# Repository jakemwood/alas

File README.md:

<picture>
  <source media="(prefers-color-scheme: dark)" srcset="docs/logo-white.svg">
  
</picture>

# ALAS (Automatic Live Audio Streamer)

## Support / Donationware

Commercial support is available for purchase from Ridgeline Radio to support our non-commercial, non-profit radio station.

Stations with budgets over $100,000/year who use ALAS are encouraged to support the project in one of a few ways:

1. Buying the equipment from us
2. Paying monthly subscription fee for the bonded VPN
3. Buying a support package

## About ALAS

ALAS is a hardware/software appliance package that automatically streams and records audio with high reliability.
Whenever audio is present on the sound card input, ALAS will begin streaming and recording. If streaming should stop,
recording will continue, and vice versa. It achieves high straming reliability through the usage of a bonding VPN, with the
designs calling for both a cellular modem and usage of built-in WiFi. ALAS will discontinue streaming and recording after
a configurable period of silence.

## Project Navigation

### alas

The main application, written in Rust, which is deployed onto a Raspberry Pi. It is responsible for:

* Allowing for easy field configuration of the appliance via a WiFi access point
* Managing the WiFi state once configured by the end user
* Manging the cellular state once configured by the end user
* Continuously monitoring input audio signal to determine when audio is being input
* Stream audio to Icecast when audio is present
* Providing a web interface for end users to administer the device
* Ensuring audio traffic is using the appropriate Engarde Wireguard interface

### cad

You'll find FreeCAD and STEP files in this folder for fabricating the rack mountable case.

### docs

You'll find instructions on how to assemble the hardware and user's guide in this folder. Documentation for software
is generally found adjacent to these components.

### frontend

To save bandwidth, a static frontend is available with a configurable backend. The static frontend is found here.
This is distinct from the "deployed frontend," which is used during the initial configuration of the network settings
on the Raspberry Pi.

### infrastructure

This is the Terraform used to create the bonding VPN servers in Microsoft Azure. 

## ALAS Software Components

### alas_lib

alas_lib is meant to serve as the "brains" of the operation. However, there is some serious
separation of concerns issues here, as the main state of the application is actually held in `alas`.

### alas

This is the monolithic application that runs on the Raspberry Pi.

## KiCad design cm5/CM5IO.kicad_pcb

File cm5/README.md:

# Alas IO Board

A custom Raspberry Pi 5 Compute Module board for Alas

Forked from the open source Raspberry Pi 5 Compute Module IO board

Modified by [Jurgen Bayer](https://www.fiverr.com/jurgenexpert/design-pcb-for-raspberry-pi-compute-module-cm4-cm5-carrier-board-cm5-io-board)

# File structure

`AlasIO` - the KiCAD files that are relevant.
`Logo Footprints` - the KiCAD footprints for the Ridgeline Radio and ALAS logos

All others are earlier attempts, revisions, drafts, etc.

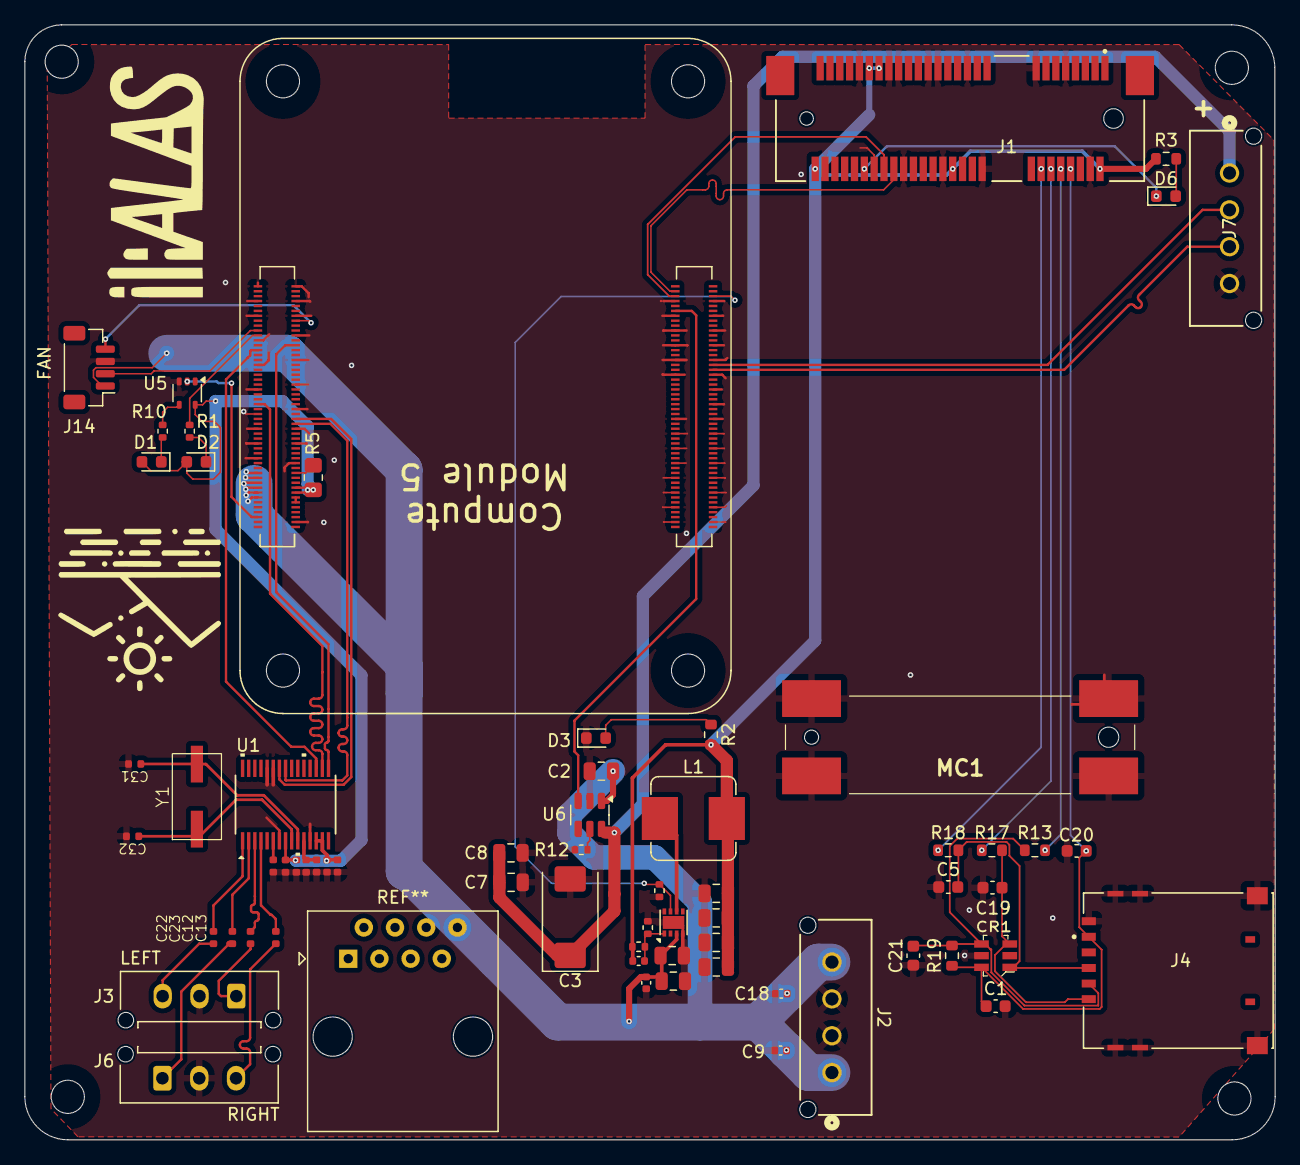
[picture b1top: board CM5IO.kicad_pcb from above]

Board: 4 copper layers, 101.9 x 90.8 mm, 69 parts (0 on the bottom side), 50 nets.

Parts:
C1: 0.1uF; C_0603_1608Metric
C2, C4, C6, C7, C8, C14, C15, C16, C17: 10u; C_0805_2012Metric
C3: 100uF; CP_EIA-7343-31_Kemet-D
C5, C19, C20, C21: 33pF; C_0603_1608Metric
C9, C10, C18: 100n; C_0402_1005Metric
C11: 4.7nF; C_0402_1005Metric
C12, C13, C22, C23, C25, C27, C29: 10uF; C_0402
C24: 1uF; C_0402
C26, C28, C30: 100nF; C_0402
C31, C32: 15pF; C_0402
CR1: DALC208SC6; SOT23-6L
D1, D3, D6: LED Red; LED_0603_1608Metric
D2: LED Green; LED_0603_1608Metric
H2, H3, H6, H8: MountingHole; MountingHole_2.7mm_M2.5_DIN965
J1: 67910-5700; MOLEX_67910-5700
J2: 1x4; CONN_SD-43650-006_04_MOL 1x4
J3, J6: Conn_01x03; Molex_Micro-Fit_3.0_43650-0315_1x03_P3.00mm_Vertical
J4: 0786463001; MOLEX_0786463001
J7: Conn_01x04; CONN_SD-43650-006_04_MOL 1x4
J14: JST_SHBM04B-SRSS-TB; JST_SH_BM04B-SRSS-TB_1x04-1MP_P1.00mm_Vertical
L1: 2.2uH; L_Bourns_SRP7028A_7.3x6.6mm
MC1: 480994000
Module1: ComputeModule5-CM5; Raspberry-Pi-5-Compute-Module
R1, R10: 1k; R_0402_1005Metric
R2, R3: 330; R_0603_1608Metric
R5: 0R; R_0805_2012Metric_Pad1.20x1.40mm_HandSolder
R12: 15K 1%; R_0402_1005Metric
R13, R17, R18: 22R; R_0603_1608Metric
R14: 100K 1%; R_0402_1005Metric
R15: 10K 1%; R_0402_1005Metric
R16: 2.2K 1%; R_0402_1005Metric
R19: 15K; R_0603_1608Metric
U1: PCM1863DBT; DBT30_TEX
U5: 74LVC1G07SE-7; SOT-353_SC-70-5
U6: AP22653W6; SOT-23-6
U8: AP3441SHE-7B; DFN-8-1EP_2x2mm_P0.5mm_EP1.05x1.75mm
Y1: Crystal (24.576MHz); S47SMD

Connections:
/+3.3v: C25.2, C26.2, C27.2, C28.1, D1.2 (A), D2.2 (A), Module1.84 (+3.3v_(Output)), Module1.86 (+3.3v_(Output)), R5.1, U1.8 (AVDD), U1.13 (DVDD), U1.14 (IOVDD), U5.5 (VCC)
/+5v: C2.1, C4.1, C6.1, C9.1, C10.1, C18.1, J2.1, J2.4, J14.1, Module1.77 (+5v_(Input)), Module1.79 (+5v_(Input)), Module1.81 (+5v_(Input)), Module1.83 (+5v_(Input)), Module1.85 (+5v_(Input)), Module1.87 (+5v_(Input)), U6.1 (IN), U8.3 (VIN)
/CM5_GPIO ( Ethernet, GPIO, SDCARD)/+1.8v: Module1.88 (+1.8v_(Output)), Module1.90 (+1.8v_(Output))
/CM5_GPIO ( Ethernet, GPIO, SDCARD)/Audio/LDO: C29.2, C30.1, U1.11 (LDO)
/CM5_GPIO ( Ethernet, GPIO, SDCARD)/Audio/LN: C22.1, J3.3
/CM5_GPIO ( Ethernet, GPIO, SDCARD)/Audio/LP: C12.1, J3.1
/CM5_GPIO ( Ethernet, GPIO, SDCARD)/Audio/RN: C23.1, J6.1
/CM5_GPIO ( Ethernet, GPIO, SDCARD)/Audio/RP: C13.1, J6.3
/CM5_GPIO ( Ethernet, GPIO, SDCARD)/Audio/VIN1M: C22.2, U1.1 (VINL2/VIN1M)
/CM5_GPIO ( Ethernet, GPIO, SDCARD)/Audio/VIN1P: C12.2, U1.3 (VINL1/VIN1P)
/CM5_GPIO ( Ethernet, GPIO, SDCARD)/Audio/VIN2M: C23.2, U1.2 (VINR2/VIN2M)
/CM5_GPIO ( Ethernet, GPIO, SDCARD)/Audio/VIN2P: C13.2, U1.4 (VINR1/VIN2P)
/CM5_GPIO ( Ethernet, GPIO, SDCARD)/Audio/XI: C31.1, U1.10 (XI), Y1.2
/CM5_GPIO ( Ethernet, GPIO, SDCARD)/Audio/XO: C32.1, U1.9 (XO), Y1.1
/CM5_GPIO ( Ethernet, GPIO, SDCARD)/GPIO2: Module1.58 (GPIO2), U1.23 (MOSI/SDA)
/CM5_GPIO ( Ethernet, GPIO, SDCARD)/GPIO3: Module1.56 (GPIO3), U1.24 (MC/SCL)
/CM5_GPIO ( Ethernet, GPIO, SDCARD)/GPIO18: Module1.49 (GPIO18), U1.17 (BCK)
/CM5_GPIO ( Ethernet, GPIO, SDCARD)/GPIO19: Module1.26 (GPIO19), U1.16 (LRCK)
/CM5_GPIO ( Ethernet, GPIO, SDCARD)/GPIO20: Module1.27 (GPIO20), U1.18 (DOUT)
/CM5_GPIO ( Ethernet, GPIO, SDCARD)/GPIO_VREF: Module1.78 (GPIO_VREF(1.8v/3.3v_Input)), R5.2
/CM5_GPIO ( Ethernet, GPIO, SDCARD)/PWM: J14.2, Module1.19 (FAN_PWM)
/CM5_GPIO ( Ethernet, GPIO, SDCARD)/TACHO: J14.4, Module1.16 (FAN_TACHO)
/CM5_GPIO ( Ethernet, GPIO, SDCARD)/nPWR_LED: Module1.95 (LED_nPWR), U5.2
/CM5_HighSpeed/PCIE_PWR_EN: Module1.106 (PCIE_PWR_EN), R14.1, U8.7 (EN)
/CM5_HighSpeed/USB2_N: J1.36, Module1.103 (USB2_N)
/CM5_HighSpeed/USB2_P: J1.38, Module1.105 (USB2_P)
/CM5_HighSpeed/USB3-0-D_N: J7.3, Module1.136 (USB3-0-D_N)
/CM5_HighSpeed/USB3-0-D_P: J7.2, Module1.134 (USB3-0-D_P)
/CM5_HighSpeed/VBUS: C3.1, C7.1, C8.1, J7.1, U6.6 (OUT)
/CM5_HighSpeed/VBUS_EN: Module1.111 (VBUS_EN), U6.3 (EN)
/Cellular/FB: C11.2, R15.2, R16.1, U8.1 (FB)
/Cellular/LED_WWAN: D6.1 (K), J1.42
/Cellular/M2_3v3: C11.1, C14.1, C15.1, C16.1, C17.1, J1.2, J1.24, J1.39, J1.41, J1.52, L1.2, R2.2, R3.2, R15.1
/Cellular/SIM_CLK: J1.12, R17.1
/Cellular/SIM_DATA: J1.10, R13.2
/Cellular/SIM_RST: J1.14, R18.1
/Cellular/SIM_VDD: C1.1, C20.1, CR1.6 (I/O4), J1.8, J4.C1 (VCC), R19.1
GND: C1.2, C2.2, C3.2, C4.2, C5.1, C6.2, C7.2, C8.2, C9.2, C10.2, C14.2, C15.2, C16.2, C17.2, C18.2, C19.1, C20.2, C21.2, C24.1, C25.1, C26.1, C27.1, C28.2, C29.1, C30.2, C31.2, C32.2, CR1.5 (REF1), D3.1 (K), J1.4, J1.9, J1.15, J1.18, J1.21, J1.26, J1.27, J1.29, J1.34, J1.35, J1.37, J1.40, J1.43, J1.50, J2.2, J2.3, J3.2, J4.C5 (GND), J4.G1 (GND__1), J4.G2 (GND__2), J4.G3 (GND__3), J4.G4 (GND__4), J4.G5 (GND__5), J4.G6 (GND__6), J6.2, J7.4, J14.3, MC1.1, MC1.2, MC1.3, MC1.4, Module1.1 (GND), Module1.2 (GND), Module1.7 (GND), Module1.8 (GND), Module1.13 (GND), Module1.14 (GND), Module1.22 (GND), Module1.23 (GND), Module1.32 (GND), Module1.33 (GND), Module1.42 (GND), Module1.43 (GND), Module1.52 (GND), Module1.53 (GND), Module1.59 (GND), Module1.60 (GND), Module1.65 (GND), Module1.66 (GND), Module1.71 (GND), Module1.74 (GND), Module1.98 (GND), Module1.107 (GND), Module1.108 (GND), Module1.113 (GND), Module1.114 (GND), Module1.119 (GND), Module1.120 (GND), Module1.125 (GND), Module1.126 (GND), Module1.131 (GND), Module1.132 (GND), Module1.137 (GND), Module1.138 (GND), Module1.144 (GND), Module1.150 (GND), Module1.155 (GND), Module1.156 (GND), Module1.161 (GND), Module1.162 (GND), Module1.167 (GND), Module1.168 (GND), Module1.173 (GND), Module1.174 (GND), Module1.179 (GND), Module1.180 (GND), Module1.185 (GND), Module1.186 (GND), Module1.191 (GND), Module1.192 (GND), Module1.197 (GND), Module1.198 (GND), R12.2, R14.2, R16.2, U1.7 (AGND), U1.12 (DGND), U1.25 (MS/AD), U1.26 (MD0), U5.3 (GND), U6.2 (GND), U8.4 (PGND), U8.8 (SGND), U8.9 (PAD)
unnamed: C5.2, CR1.1 (I/O1), J4.C2 (RST), R18.2
unnamed: C19.2, CR1.3 (I/O2), J4.C3 (CLK), R17.2
unnamed: C21.1, CR1.4 (I/O3), J4.C7 (I/O), R13.1, R19.2
unnamed: D1.1 (K), R10.1
unnamed: D2.1 (K), R1.1
unnamed: D3.2 (A), R2.1
unnamed: D6.2 (A), R3.1
unnamed: Module1.21 (LED_nACT), R1.2
unnamed: R10.2, U5.4
unnamed: C24.2, U1.6 (VREF)
unnamed: R12.1, U6.5 (ILIM)
unnamed: L1.1, U8.6 (LX)

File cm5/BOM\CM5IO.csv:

"Reference","Value","Footprint","Datasheet","Qty","Field4","Field5","Field6","Field7","Field8","Part Description","DNP"
"C1","0.1uF","Capacitor_SMD:C_0603_1608Metric","~","1","","","","","","",""
"C2,C4,C6,C7,C8,C14,C15,C16,C17","10u","Capacitor_SMD:C_0805_2012Metric","https://search.murata.co.jp/Ceramy/image/img/A01X/G101/ENG/G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","9","Digikey","490-14381-1-ND","GRM21BR71A106KA73L","Murata","111893011","10uF 10% 10V Ceramic Capacitor X7R 0805 (2012 Metric)",""
"C3","100uF","Capacitor_Tantalum_SMD:CP_EIA-7343-31_Kemet-D","~","1","Mouser","667-EEF-CX0J101R","","Panasonic","","Capacitor, SP-Cap, 100u, 6.3V, 15mR ESR",""
"C5,C19,C20,C21","33pF","Capacitor_SMD:C_0603_1608Metric","~","4","","","","","","",""
"C9,C10,C18,C23,C25,C26,C29,C31","100n","Capacitor_SMD:C_0402_1005Metric","https://search.murata.co.jp/Ceramy/image/img/A01X/G101/ENG/G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","8","Farnell","2611911","RM EMK105 B7104KV-F","TAIYO YUDEN EUROPE GMBH","110091611","0.1uF 10% 16V Ceramic Capacitor X7R 0402 (1005 Metric)",""
"C11","4.7nF","Capacitor_SMD:C_0402_1005Metric","~","1","","","","","","4.7nF capacitor 0402",""
"C12,C13","1uF","digikey-footprints:0603","~","2","","","","","","",""
"C24","1uF","digikey-footprints:0805","~","1","","","","","","",""
"C27,C28,C30","10uF","Capacitor_SMD:CP_Elec_6.3x5.9","~","3","","","","","","",""
"CR1","DALC208SC6","digikey-footprints:SOT23-6L","DALC208SC6","1","","","","","","",""
"D1,D3,D4,D6","LED Red","LED_SMD:LED_0603_1608Metric","http://optoelectronics.liteon.com/upload/download/DS22-2000-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","4","Digikey ","LTST-S270KRKT","SML-A12U8TT86Q","Rohm","650295101","Red 620nm LED Indication - Discrete 2.2V 2-SMD, No Lead",""
"D2","LED Green","LED_SMD:LED_0603_1608Metric","http://optoelectronics.liteon.com/upload/download/DS22-2000-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","1","Digikey ","LTST-S270KGKT","SML-A12M8TT86N","Rohm","650263301","Green 572nm LED Indication - Discrete 2.2V 2-SMD, No Lead",""
"J1","67910-5700","0679105700:MOLEX_67910-5700","","1","","","","","","",""
"J2","B2B-XH-A_LF__SN_","digikey-footprints:PinHeader_1x2_P2.5mm_Drill1.1mm","http://www.jst-mfg.com/product/pdf/eng/eXH.pdf","1","","","","","","",""
"J4","0786463001","0786463001:MOLEX_0786463001","","1","","","","","","",""
"J5","USB3_A","Connector_USB:C168717","~","1","","","","","","",""
"J6","Conn_02x03_Counter_Clockwise","Connector_PinHeader_2.54mm:PinHeader_2x03_P2.54mm_Vertical","~","1","","","","","","",""
"J7","Conn_01x04","Connector_JST:JST_EH_B4B-EH-A_1x04_P2.50mm_Vertical","~","1","","","","","","",""
"J14","JST_SHBM04B-SRSS-TB","Connector_JST:JST_SH_BM04B-SRSS-TB_1x04-1MP_P1.00mm_Vertical","","1","","SHBM04B-SRSS-TB","SHBM04B-SRSS-TB","JST","","4 pin vertical 1mm pitch connector",""
"L1","2.2uH","CM5IO:L_Bourns_SRP5030CC","https://www.bourns.com/docs/product-datasheets/srp5030cc.pdf","1","","SRP5030CC-2R2M","SRP5030CC-2R2M","Bourns","","Inductor, SMT, 2520, 2u2, IRMS=7A, ISAT=8A, DCR=0.032R",""
"M1","M.2 Screw","","","1","","","","","","M.2 Screw",""
"M2,M3,M4,M5","M.2 Solder Nut","","","4","","","","","","Solder nut for M.2 slot",""
"MC1","~","KiCad:480994000","","1","","","","","","",""
"Module1","ComputeModule5-CM5","CM5IO:Raspberry-Pi-5-Compute-Module","","1","Amphenol","2x 10164227-1001A1RLF","2x 10164227-1001A1RLF","Hirose","","100 Position Connector Receptacle, Center Strip Contacts Surface Mount Gold",""
"R1,R10","1k","Resistor_SMD:R_0402_1005Metric","https://fscdn.rohm.com/en/products/databook/datasheet/passiv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","2","Farnell","9239235","RK73H1ETTP1001F","KOA EUROPE GMBH","125049511","Resistor 1K M1005 1% 63mW",""
"R2,R3,R11","330","Resistor_SMD:R_0603_1608Metric","~","3","","","","","","",""
"R5","0R","Resistor_SMD:R_0805_2012Metric_Pad1.20x1.40mm_HandSolder","https://fscdn.rohm.com/en/products/databook/datasheet/passiv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","1","Farnell","9233750","MCR10EZPJ000","Rohm","121629591","Resistor 0R M2012 5% ",""
"R12","15K 1%","Resistor_SMD:R_0402_1005Metric","https://fscdn.rohm.com/en/products/databook/datasheet/passiv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","1","Farnell","9239375","MCR01MZPF1502","Rohm","120891581","Resistor 15K M1005 1% 63mW",""
"R13,R17,R18","22R","Resistor_SMD:R_0603_1608Metric","~","3","","","","","","",""
"R14","100K 1%","Resistor_SMD:R_0402_1005Metric","https://fscdn.rohm.com/en/products/databook/datasheet/passiv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","1","Farnell","","MCR01MZPF1003","Rohm","","Resistor 100K M1005 1% 63mW",""
"R15","10K 1%","Resistor_SMD:R_0402_1005Metric","https://fscdn.rohm.com/en/products/databook/datasheet/passiv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","1","Farnell","","MCR01MZPF1002","Rohm","","Resistor 10K M1005 1% 63mW",""
"R16","2.2K 1%","Resistor_SMD:R_0402_1005Metric","https://fscdn.rohm.com/en/products/databook/datasheet/passiv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","1","Farnell","","","","","Resistor 2.2K M1005 1% 63mW",""
"R19","15K","Resistor_SMD:R_0603_1608Metric","~","1","","","","","","",""
"U1","CAT24C128","Package_SO:SOIC-8_5.3x6.2mm_P1.27mm","https://www.onsemi.com/pub/Collateral/CAT24C128-D.PDF","1","","","","","","",""
"U2","TLV320ADC6120IRTER","TLV320ADC6120IRTER:IC_TLV320ADC6120IRTER","","1","","","","","","",""
"U5","74LVC1G07SE-7","Package_TO_SOT_SMD:SOT-353_SC-70-5","https://www.diodes.com/assets/Datasheets/74LVC1G07.pdf","1","Farnell","2425492","74LVC1G07SE-7","Diodes","","Buffer, Non-Inverting 1 Element 1 Bit per Element Open Drain Output SOT-353",""
"U6","AP22653W6","Package_TO_SOT_SMD:SOT-23-6","https://www.diodes.com/assets/Datasheets/AP255x.pdf","1","Digikey","31-AP22653W6-7CT-ND","AP22653W6","Diodes","","Power Switch/Driver 1:1 P-Channel 2.1A SOT-23-6",""
"U8","AP3441SHE-7B","Package_DFN_QFN:DFN-8-1EP_2x2mm_P0.5mm_EP1.05x1.75mm","https://www.diodes.com/assets/Datasheets/AP3441-L.pdf","1","","AP3441SHE-7B","AP3441SHE-7B","Diodes","","3A DC-DC converter",""

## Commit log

2024-12-19 Checkpoint -- it compiles and writes stuff to the LCD display
2024-12-19 Initial AI frontend
2024-12-19 Formatting
2024-12-19 Success at connecting to access point via web browser
2024-12-19 Remove dead imports
2024-12-19 Working volume meter
2024-12-19 Relatively working LCD screen!
2024-12-19 too many changes
2024-12-19 Much nicer frontend
2024-12-19 Refactor to fix unit tests and clean up screen import cycles
2024-12-19 small justfile add for frontend
2024-12-19 install alsa
2024-12-19 install alsa 2
2024-12-19 install lib-alsa
2024-12-19 libudev install
2024-12-21 Well it WAS working
2024-12-22 approximately the correct configuration for working audio
2024-12-22 Write software shutdown to display on graceful program exit
2024-12-22 Audio is in a great spot now with Icecast and recording working via the bus
2024-12-23 Remove .idea from git
2024-12-23 Rename web to alas, and ridgeline references to alas
2024-12-23 Setup script + other things
2024-12-23 IP address screen works, but state mgmt needs a ton of work
2024-12-23 Add just test
2024-12-23 Formatting + renames
2024-12-23 Add ability to create the configuration hotspot
2024-12-23 Unit tests for menu screen and whatnot
2024-12-30 * Refactors on WiFi configuration situation * Fixes on the configuration menu
2024-12-30 Enormous re-org
2024-12-30 re-org part 2
2024-12-30 Working SSE for sending volume data but it is *really* fast, needs base64 encoding for floats
2024-12-30 some rust fixes
2024-12-31 Add cad files
2025-01-31 add throttle for voulme messages
2025-02-02 Enlarge pockets for buttons and LEDs on display, fix C14 size, fix height of base, improve the top
2025-03-03 something terrible happened to my file
2025-03-03 made c14 slightly larger, adjusted thicknesses for new materials
2025-03-03 new parts ordered, v3 confirmed
2025-03-09 Find the LCD display dynamically
2025-03-09 reformat, add some web endpoints, authentication, wifi status endpoint
2025-03-09 wifi status endpoint
2025-03-10 Auth + network status + cellular stuff
2025-03-11 Reformat frontend and add admin for icecast interface along with re-connect stuff
2025-03-12 Threading refactors and frontend progress
2025-03-14 A bunch of threading non-sense to allow for safe/clean exits
2025-03-15 Refactor, reformat, more threading, more more more
2025-03-15 GitHub workflow that probably will not work
2025-03-15 one more ci
2025-03-15 ai ci
2025-03-15 Run CI on ARM to match Raspberry Pi
2025-03-15 [ci] install all the deps
2025-03-16 Add cellular stuff
2025-03-16 dark mode readme
2025-03-16 Approximate script to set up Engarde server
2025-03-16 fix bugs
2025-03-16 Engarde server config
2025-03-16 save config too
2025-03-17 minor commit
2025-03-17 Success! Able to disconnect/connect the LCD display at will
2025-03-17 Emoji logs
2025-03-17 Authentication
2025-03-23 Add "hole" for grounding stud
2025-04-08 Don't crash if we can't find a modem
2025-04-16 Dropbox authentication + a work-in-progress "upload progress" screen
2025-04-17 Dropbox uploads are working, but the AI code is messy
2025-04-26 Add CM5 base board files, clean up CAD
2025-04-26 Latest Cm5 work
2025-04-27 Way too much has changed...
2025-04-27 things are still not connected
2025-04-28 new cm5 ordered!
2025-04-28 1. Fix hole size for JLCPCB limitations on testing 2. Create fix_bom script which will correct the quantity and locations of the Raspberry Pi 5 Compute Module pins
2025-04-28 Added screws and hardware to the face Imported new PCB as step (still need to redraw the standoffs)
2025-05-01 Hopefully these are the corrected parts, need to cross-reference the BOM to what was ordered
2025-05-01 Project clean up and WIP CAD model for enclosure
2025-05-15 Uh in this version, I have made the 5v trace fatter
2025-05-17 Ordered v2 PCB
2025-05-17 remove dead changelog
2025-05-17 Make a ground plane (#4)
    * Way too much has changed...
    * things are still not connected
    * things are still not connected
    * new cm5 ordered!
    * 1. Fix hole size for JLCPCB limitations on testing
    2. Create fix_bom script which will correct the quantity and locations of the Raspberry Pi 5 Compute Module pins
2025-05-29 Oops, basically brand new ADC design using a new chip
2025-06-12 Working PCB and working driver, sort of
2025-06-12 --amend
2025-06-12 PCM1863 switchover (#5)
    * Oops, basically brand new ADC design using a new chip
    * Working PCB and working driver, sort of
    * --amend
2025-06-13 Ordered next round revision of sheet metal
2025-06-13 Fix the usb port (just in case) #1
2025-07-16 Relatively final revision on the STEP files
2025-07-16 backup changes on cm5
2025-07-17 A ton of Dropbox, recording, and PCM1863 compatibility work
2025-07-18 Fix #7
2025-07-18 Attempt to make github action work
2025-07-18 no private repo availability for arm runners
2025-07-18 Implement #8 and also try again to fix action
2025-07-18 Ubuntu 24.04 for just
2025-07-18 fix justfile
2025-07-18 Try pinning just version, print error on reboot/shutdown fail
2025-07-18 Try to pin just
2025-07-18 Rename cross.toml
2025-07-18 Completes #8
2025-07-18 Dropbox button fix #10
2025-07-18 Claude attempt to fix action
2025-07-18 Dropbox frontend stuff
2025-07-18 another try
2025-07-18 alsa cross build
2025-07-19 silly change for cf page push
2025-07-19 wrangelr jsonc
2025-07-19 Prettier
2025-07-20 wg-quick redundancy
2025-07-20 Delete files, server readme, etc
    Huge progress on redundancy, although code is a disaster
    Frontend upates
2025-07-22 Redundancy (#12)
2025-07-22 Fix wifi config + some home screen stuff for cellular, it still does not work
2025-07-22 Fix wifi config + some home screen stuff for cellular, it still does not work (#14)
2025-07-22 Disable ipv6 on wwan (screws with routing) and make config.json flexible for eventual installation in /usr/bin
2025-07-23 Disable ipv6 on wwan (screws with routing) and make config.json flexible for eventual installation in /usr/bin (#15)
2025-07-23 Make changes for /usr/lib installation
2025-07-23 Make changes for /usr/lib installation (#16)
2025-07-23 Cellular + redundancy changes
2025-07-23 Cellular + redundancy changes (#17)
2025-07-23 idk what the hell happened here
2025-07-23 idk what the hell happened here (#18)
    ### TL;DR
    Updated file paths to use `/var/lib/alas` directory and improved audio device selection to target PCM1863 hardware.
    ### What changed?
    - Changed configuration file path from `/etc/alas/config.json` to `/var/lib/alas/config.json`
    - Updated audio recording to save files to `/var/lib/alas/audio/` directory
    - Modified audio device selection to specifically target PCM1863 devices
2025-07-23 Deep frontend formatting
2025-07-23 Deep frontend formatting (#19)
2025-07-23 Random bug fixes and new WiFi interface
2025-07-23 Random bug fixes and new WiFi interface (#20)
    ### TL;DR
    Enhanced WiFi network management with a new UI for scanning and connecting to available networks, and improved error handling in the cellular and WiFi connection code.
    ### What changed?
    - Added a new `NetworkCard` component to display available WiFi networks with signal strength indicators
    - Implemented WiFi network scanning functionality in the frontend
    - Updated the Network page to show available networks and allow connecting to them
2025-07-23 State was behind held for too long, crashing the program
2025-07-23 State was behind held for too long, crashing the program (#21)
    ### TL;DR
    Improved thread management for LCD display and fixed a potential deadlock in the Dropbox authentication flow.
    ### What changed?
    - Modified the LCD display thread to use `spawn_blocking` with a dedicated runtime instead of a regular tokio spawn
    - Fixed a potential deadlock in the Dropbox authentication flow by:
    - Reading the config under a read lock first
2025-07-26 Critical state fix plus unauthenticated nicety
2025-07-26 Critical state fix plus unauthenticated nicety (#22)
    ### TL;DR
    Improved error handling in both the backend audio connection and frontend API requests.
    ### What changed?
    - Fixed a potential deadlock in the Icecast connection logic by replacing `blocking_read()` with a non-blocking `try_read()` approach
    - Added comprehensive authentication error handling to the frontend API:
    - All API requests now check for 401/403 status codes
2025-07-26 Fix default engarde configuration to exclude the wireguard interface
2025-07-26 Fix default engarde configuration to exclude the wireguard interface (#23)
2025-07-27 Assume https for tunnels now
2025-07-27 Assume https for tunnels now (#24)
2025-07-27 Authenticated API also needs the same treatment
2025-08-10 Webhook claude
2025-08-10 try to build on pi natively
2025-08-10 fix justfile?
2025-08-10 args
2025-08-10 Upload artifact
2025-08-10 debug workflow
2025-08-10 annoying
2025-08-10 toolchain version
2025-08-10 satisfy the build
2025-08-10 continue to satisfy
2025-08-11 ci fix?
2025-08-11 let's try this
2025-08-11 make a release build instead
2026-01-10 Webhook claude (#25)
    * Webhook claude
    * try to build on pi natively
    * fix justfile?
    * args
    * Upload artifact
    * debug workflow
2026-01-10 Tests for webhook
2026-01-11 update cargo
2026-01-11 Tests for webhook (#26)
    * Tests for webhook
    * update cargo
2026-01-11 Add claude instructions for testing
2026-01-13 Add matrix orbital setup code
2026-01-13 Getting started on StudioHub adapter
2026-01-13 Allow null configs for things
2026-01-19 Latest improvements
2026-01-23 Changes to redundancy manager architecture (I think)
2026-01-23 Add libshout3 to setup
2026-03-25 Allow http, maybe?
2026-03-25 Allow http, maybe? (#31)
2026-03-25 fix single page app
2026-04-05 WiFi, SSL, and static fixes
2026-04-05 Allow null configs for things (#28)
2026-04-05 Changes to redundancy manager architecture (I think) (#29)
2026-04-05 Allow all CORS origins, you just never know
2026-04-06 Add libshout3 to setup (#30)
